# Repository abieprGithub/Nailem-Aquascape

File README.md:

# Nailem: Smart Aquascape

As the name suggests, N**ai**lem is an AIoT-powered highly automated aquascape maintenance system, originally designed for Nilem fish (Osteochilus Vittatus):

<br>

🐟 Why Nilem in particular?

1. They're awesome
2. They're tuff (as in they can live in harsh conditions)
3. They're edible (yum)
4. They're common in my nation (Indonesia!)
5. They're reasonably sized (for food fish, at least)

### ❗ But more importantly,
This is **not** limited only to Nilem fish, and it will be designed to be scalable and flexible to meet the living conditions of most other fish, across a wide range of scale.
Of course, community contributions help in adapting this to a wider range of fish, though I haven't given myself time to learn how to manage contributions yet.

I've came up with this to solve a very real problem:
1) Raising food fish is a challenging and long process
2) I'm lazy as hell
3) Urban farming shouldn't be limited to crops, but livestock too

## Quick navigation

[🛠️ Technical Functions](detailed-functions) | [⚠️ Disclaimers](disclaimer) | [📜 Bulletin](bulletin)

(doesn't work yet, my bad)

<br>

## ⚙️ Functions

*Note: The following 3D model is old, and I will make a new one from the ground up soon.*

## 🛠️ Technical
It packs a whole load of functions. At its core, it's split between two subsystems: Real time control & AI compute.
At its core is an ESP32-S3 as a real time controller, which is kind of a perfect fit for this since I ended up utilizing almost its full potential.
To clarify a bit, what I mean by 'AI' before is actually just computer vision.
For that, this can be fitted with pretty much any low power computer that has USB or UART support, preferably SBCs designed for edge AI.
The NVIDIA Jetson Orin or the Rasperry Pi 5 + AI HAT should work well.
The thing is, the real time subsystem can exist as a standalone system, omitting the computer vision features entirely if the budget didn't allow.
However, it's 2026 and IoT alone is getting a little bit outdated.

<br>

<br>

### Detailed functions

*Programming or build hasn't started yet, but this gives you an idea of what I wanted to create.* 

**Primary Automation Features:**
1) 💦 Surface cleaning
2) 🌡️ Temperature Regulation
3) 🥄 Feeding
4) 💡Lighting
5) 🔄 Water Change

**Monitored parameters:**
1) Water Temperature
2) Water pH
3) Water TDS
4) Water Turbidity
5) Ambient temperature
6) Ambient humidity
7) Ambient lighting
8) Power consumption

**IoT features:**
1) Web Dashboard
2) API
3) OTA Firmware Update
4) 

**AI Features:**
1) Fish behavior detection
2) Anomaly detection
3) Egg detection (hopefully 😭)

**Miscellaneous features for the sake of the developer and or the user**
1) Two status ARGB LEDs on the board
2) Header for an external ARGB
3) UART debug header
4) USB-C data-only receptacle
5) Highly modular design, both physically and electrically. 

## Disclaimer
This used to be my 8th grade engineering project. However, after the project officially closes, I was NOT satisfied with how this turned out (it was still under 50% done), so I took over this entire project after ensuring that my team is okay with it. 
With that, kudos to my goated team for their work, even though I was responsible for 80% of the technical work:

<br>

Abie (myself) - Programmer, leader; Akbar - Mechanic; Adzka - Mechanic; <br>
Nabil - Management; Shifa - Scientist; Kirana - Media;

<br>
This did technically start before the Hack Club Stardance YSWS, but the amount of revisions made AFTER it started make this practically a new project tbh.
However, I'm still going to state that this project started before the season anyways.

## Bulletin

*This section is intended to show the latest updates, devlogs, or things you should know, and is updated reguarly!*

### 15th of September 2026

While waiting for the PCB to arrive, I took some time to create the CAD of the Aquascape. <br>
P.S, I haven't pushed the CAD to main since it's a little too large, I'll optimize it. <br>
Currently, it has seen great progress and I have created a few things: <br>
1) The aquarium glass
2) Most of the surface cleaning gantry mechanism, which includes:
3) Stepper motor Bracket
4) Endstops
5) Frame
6) Pulleys
7) Ultrasonic sensor bracket
8) Control box

A lot of things are still yet to be implemented, so let things continue. <br>
Meanwhile, here are some latest pictures.

### 7th of September 2026

The main ESP32-S3 IO PCB iteslf has been completed, and has started its production on JLCPCB. It should arrive at my doorsteps within 10-15 days. Meanwhile, I'll be working on the CAD model of the Aquascape with all the time I had. <br>
It took a total of over 20 hours to make it pretty, both electrically, visually, and functionally, whilst also having the constraints of having to fit inside JLCPCB's economic 2 layer footprint so I don't get taxed by Indonesian customs. <br> <br>

Anyways, here are some 3D model and boardview screenshots!

<br>
Without components:

<br><br><br><br><br><br><br><br><br><br><br><br><br><br><br><br><br><br><br>

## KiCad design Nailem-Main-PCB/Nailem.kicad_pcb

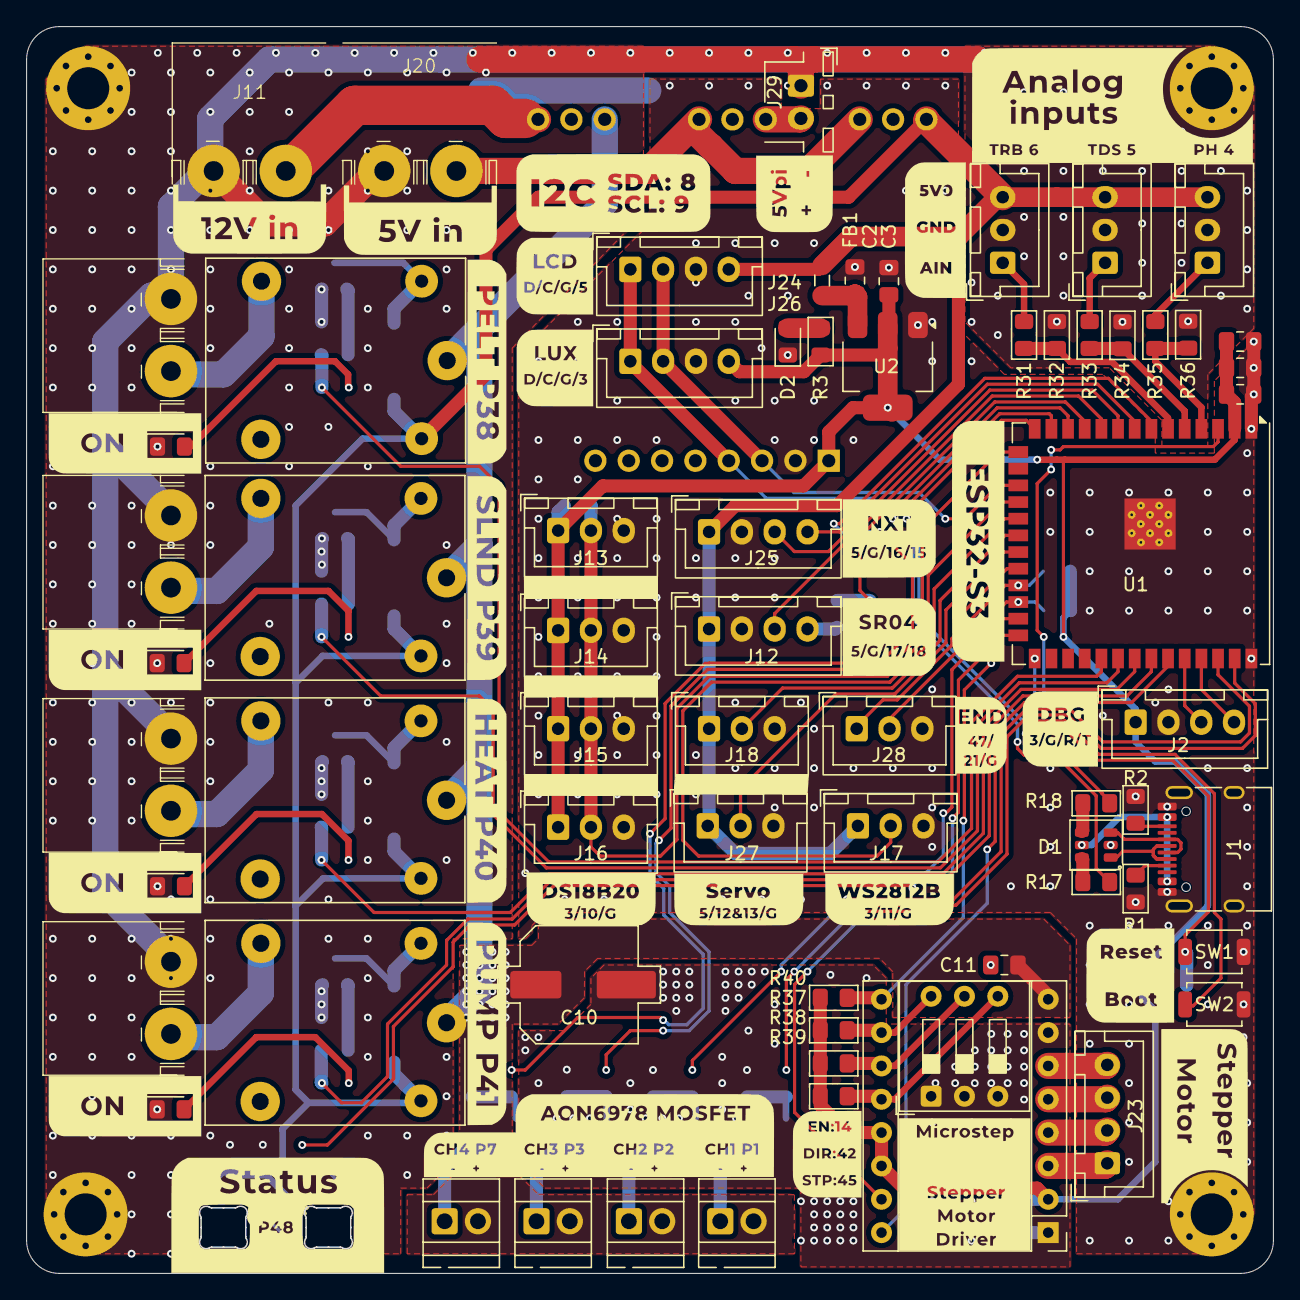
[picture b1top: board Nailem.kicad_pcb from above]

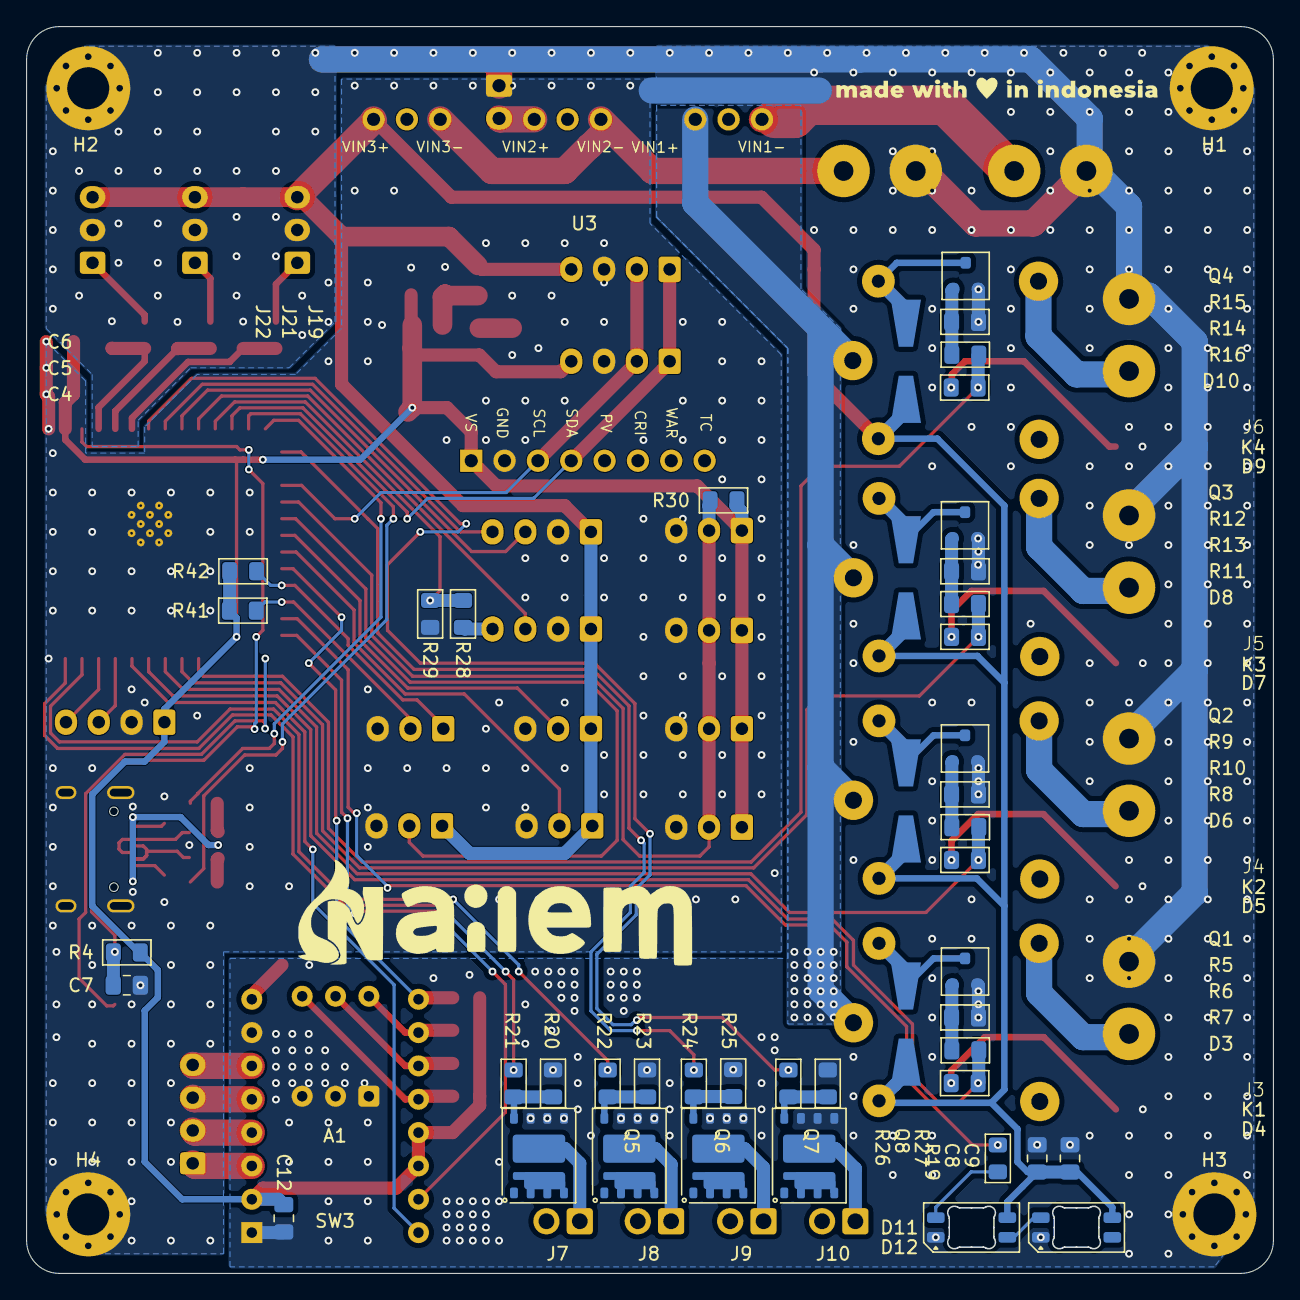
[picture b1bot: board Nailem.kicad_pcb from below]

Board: 2 copper layers, 95.0 x 95.0 mm, 118 parts (46 on the bottom side), 86 nets.

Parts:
A1: Pololu_Breakout_A4988; Pololu_Breakout-16_15.2x20.3mm
C2, C3, C4: 10uF; C_0805_2012Metric_Pad1.18x1.45mm_HandSolder
C5, C7: 1uF; C_0805_2012Metric_Pad1.18x1.45mm_HandSolder
C6, C8, C9, C11, C12: 100nF; C_0805_2012Metric_Pad1.18x1.45mm_HandSolder
C10: 100uF; C_Elec_8x10.2
D1: USBLC6-2SC6; SOT-23-6
D2, D4, D5, D7, D9: LED; LED_0805_2012Metric_Pad1.15x1.40mm_HandSolder
D3, D6, D8, D10: 1N4007; D_SMA-SMB_Universal_Handsoldering_NoSilk
D11, D12: SK6812MINI-E; LED_SK6812MINI-E_3.2x2.8mm_P1.5mm_ReverseMount
FB1: FerriteBead; L_0805_2012Metric_Pad1.05x1.20mm_HandSolder
H1, H2, H3, H4: MountingHole; MountingHole_3.2mm_M3_Pad_Via
J1: USB_OTG; USB_C_Receptacle_HRO_TYPE-C-31-M-12
J2: J_UART; JST_XH_B4B-XH-A_1x04_P2.50mm_Vertical
J3: OUT_CH1; 2EDGK_5.08_2P_M_NEW
J4: OUT_CH2; 2EDGK_5.08_2P_M_NEW
J5: OUT_CH3; 2EDGK_5.08_2P_M_NEW
J6: OUT_CH4; 2EDGK_5.08_2P_M_NEW
J7: LED_CH1; TerminalBlock_Xinya_XY308-2.54-2P_1x02_P2.54mm_Horizontal_N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
J8: LED_CH2; TerminalBlock_Xinya_XY308-2.54-2P_1x02_P2.54mm_Horizontal_N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
J9: LED_CH3; TerminalBlock_Xinya_XY308-2.54-2P_1x02_P2.54mm_Horizontal_N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
J10: LED_CH4; TerminalBlock_Xinya_XY308-2.54-2P_1x02_P2.54mm_Horizontal_N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
J11: 12VIN; 2EDGK_5.08_2P_M_NEW
J12: J_SR04; JST_XH_B4B-XH-A_1x04_P2.50mm_Vertical
J13: J_DS18B20_1; JST_XH_B3B-XH-A_1x03_P2.50mm_Vertical
J14: J_DS18B20_2; JST_XH_B3B-XH-A_1x03_P2.50mm_Vertical
J15: J_DS18B20_3; JST_XH_B3B-XH-A_1x03_P2.50mm_Vertical
J16: J_DS18B20_4; JST_XH_B3B-XH-A_1x03_P2.50mm_Vertical
J17: J_STATUS; JST_XH_B3B-XH-A_1x03_P2.50mm_Vertical
J18: J_SERVO; JST_XH_B3B-XH-A_1x03_P2.50mm_Vertical
J19: J_TURBIDITY; JST_XH_B3B-XH-A_1x03_P2.50mm_Vertical
J20: 5VIN; 2EDGK_5.08_2P_M_NEW
J21: J_TDS; JST_XH_B3B-XH-A_1x03_P2.50mm_Vertical
J22: J_PH; JST_XH_B3B-XH-A_1x03_P2.50mm_Vertical
J23: J_STEPPER; JST_XH_B4B-XH-A_1x04_P2.50mm_Vertical
J24: J_5V_LCD; JST_XH_B4B-XH-A_1x04_P2.50mm_Vertical
J25: J_5V_NEXTION; JST_XH_B4B-XH-A_1x04_P2.50mm_Vertical
J26: J_3V3_LUX; JST_XH_B4B-XH-A_1x04_P2.50mm_Vertical
J27: J_SERVO2; JST_XH_B3B-XH-A_1x03_P2.50mm_Vertical
J28: J_ENDS; JST_XH_B3B-XH-A_1x03_P2.50mm_Vertical
J29: 5VPI; JST_XH_B2B-XH-A_1x02_P2.50mm_Vertical
K1, K2, K3, K4: SANYOU_SRD_Form_C; Relay_SPDT_SANYOU_SRD_Series_Form_C_NoInSilk
Q1, Q2, Q3, Q4: MMBT2222A; SOT-23
Q5, Q6, Q7, Q8: AON6980; SO-8FL_DFN5x6
R1, R2: 5.1K; R_0805_2012Metric_Pad1.15x1.40mm_HandSolder
R3, R7, R8, R11, R14, R29, R32, R34, R36: 2K; R_0805_2012Metric_Pad1.15x1.40mm_HandSolder
R4, R20, R23, R25, R27, R37, R38, R39, R40, R41, R42: 10K; R_0805_2012Metric_Pad1.15x1.40mm_HandSolder
R5, R9, R12, R15: 100K; R_0805_2012Metric_Pad1.15x1.40mm_HandSolder
R6, R10, R13, R16, R28, R31, R33, R35: 1K; R_0805_2012Metric_Pad1.15x1.40mm_HandSolder
R17, R18: 33; R_0805_2012Metric_Pad1.15x1.40mm_HandSolder
R19: 220; R_0805_2012Metric_Pad1.15x1.40mm_HandSolder
R21, R22, R24, R26: 47; R_0805_2012Metric_Pad1.15x1.40mm_HandSolder
R30: 4.7K; R_0805_2012Metric_Pad1.15x1.40mm_HandSolder
SW1: SW_RST; SW_SPST_TS-1088-xR020
SW2: SW_BOOT; SW_SPST_TS-1088-xR020
SW3: SW_DIP_x03; SW_DIP_SPSTx03_Slide_9.78x9.8mm_W7.62mm_P2.54mm
U1: ESP32-S3-WROOM-1; ESP32-S3-WROOM-1U
U2: AMS1117-3.3; SOT-223-3_TabPin2
U3: INA3221_Module; INA3221_Module_P2.54mm_NoVPU_NoExtraGnds

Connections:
3V3LOGIC: A1.2 (VDD), A1.13 (~RESET), A1.14 (~SLEEP), C3.1, C4.1, C5.1, C6.1, C12.1, J2.1, J13.1, J14.1, J15.1, J16.1, J26.4, R3.2, R4.1, R30.1, R37.2, R38.2, R39.2, R40.2, R41.1, R42.1, U1.2 (3V3), U2.2 (VO), U3.1 (VS)
5VIN: C8.1, C9.1, D3.1 (K), D6.1 (K), D8.1 (K), D10.1 (K), D11.3 (VDD), D12.3 (VDD), FB1.1, J12.1, J17.1, J18.1, J19.3, J21.3, J22.3, J24.4, J25.1, J27.1, K1.5, K2.5, K3.5, K4.5, U3.14 (VIN3+)
5VPI: J29.2, U3.12 (VIN2+)
12V: A1.8 (VMOT), C10.1, C11.1, J7.2, J8.2, J9.2, J10.2, K1.1, K2.1, K3.1, K4.1, U3.10 (VIN1+)
CUR_N_CH1: J11.2, U3.9 (VIN1-)
CUR_N_CH2: J20.2, U3.11 (VIN2-), U3.13 (VIN3-)
DS18B20_BUS: J13.2, J14.2, J15.2, J16.2, R30.2, U1.18 (IO10)
END_XMIN: J28.1, R42.2, U1.23 (IO21)
END_XPLUS: J28.2, R41.2, U1.24 (IO47)
ESP_RX: J2.3, U1.36 (RXD0)
ESP_TX: J2.4, U1.37 (TXD0)
GND: A1.1 (GND), A1.7 (GND), C2.2, C3.2, C4.2, C5.2, C6.2, C7.2, C8.2, C9.2, C10.2, C11.2, C12.2, D1.2 (VN), D2.1 (K), D4.1 (K), D5.1 (K), D7.1 (K), D9.1 (K), D11.1 (VSS), D12.1 (VSS), H1.1 (1_1), H2.1 (1_1), H3.1 (1_1), H4.1 (1_1), J1.A1 (GND), J1.A12 (GND), J1.B1 (GND), J1.B12 (GND), J1.SH (SHIELD), J2.2, J3.2, J4.2, J5.2, J6.2, J11.1, J12.2, J13.3, J14.3, J15.3, J16.3, J17.3, J18.3, J19.2, J20.1, J21.2, J22.2, J24.3, J25.2, J26.3, J27.3, J28.3, J29.1, Q1.2 (E), Q2.2 (E), Q3.2 (E), Q4.2 (E), Q5.3 (S2), Q5.4 (S2), Q5.5 (S2), Q6.3 (S2), Q6.4 (S2), Q6.5 (S2), Q7.3 (S2), Q7.4 (S2), Q7.5 (S2), Q8.3 (S2), Q8.4 (S2), Q8.5 (S2), R1.1, R2.1, R5.1, R9.1, R12.1, R15.1, R20.2, R23.2, R25.2, R27.2, R29.1, R32.1, R34.1, R36.1, SW1.1 (A), SW2.1 (A), SW3.1, SW3.2, SW3.3, U1.1 (GND), U1.40 (GND), U1.41 (GND), U2.1 (GND), U3.2 (GND)
HCSR04_ECHO: R28.2, R29.2, U1.11 (IO18)
HCSR04_TRIG: J12.3, U1.10 (IO17)
I2C_SCL: J24.2, J26.2, U1.17 (IO9), U3.3 (SCL)
I2C_SDA: J24.1, J26.1, U1.12 (IO8), U3.4 (SDA)
IND_ARGB: R19.1, U1.25 (IO48)
LED_DRV_CH1: R21.1, U1.39 (IO1)
LED_DRV_CH2: R22.1, U1.38 (IO2)
LED_DRV_CH3: R24.1, U1.15 (IO3)
LED_DRV_CH4: R26.1, U1.7 (IO7)
NX_RX: J25.3, U1.9 (IO16)
NX_TX: J25.4, U1.8 (IO15)
unnamed: A1.4 (1A), J23.2
unnamed: A1.3 (1B), J23.1
unnamed: A1.5 (2A), J23.3
unnamed: A1.6 (2B), J23.4
unnamed: A1.10 (MS1), R37.1, SW3.6
unnamed: A1.11 (MS2), R38.1, SW3.5
unnamed: A1.12 (MS3), R39.1, SW3.4
unnamed: D1.1 (L1), J1.A7 (D-), J1.B7 (D-)
unnamed: D1.3 (L2), J1.A6 (D+), J1.B6 (D+)
unnamed: D1.5 (VP), J1.A4 (VBUS), J1.A9 (VBUS), J1.B4 (VBUS), J1.B9 (VBUS)
unnamed: D2.2 (A), R3.1
unnamed: D3.2 (A), K1.2, Q1.3 (C)
unnamed: D4.2 (A), R7.1
unnamed: D5.2 (A), R8.1
unnamed: D6.2 (A), K2.2, Q2.3 (C)
unnamed: D7.2 (A), R11.1
unnamed: D8.2 (A), K3.2, Q3.3 (C)
unnamed: D9.2 (A), R14.1
unnamed: D10.2 (A), K4.2, Q4.3 (C)
unnamed: D11.2 (DIN), R19.2
unnamed: D11.4 (DOUT), D12.2 (DIN)
unnamed: J1.A5 (CC1), R1.2
unnamed: J1.B5 (CC2), R2.2
unnamed: J3.1, K1.3
unnamed: J4.1, K2.3
unnamed: J5.1, K3.3
unnamed: J6.1, K4.3
unnamed: J7.1, Q5.7 (C)
unnamed: J8.1, Q6.7 (C)
unnamed: J9.1, Q7.7 (C)
unnamed: J10.1, Q8.7 (C)
unnamed: J12.4, R28.1
unnamed: J19.1, R31.2
unnamed: J21.1, R33.2
unnamed: J22.1, R35.2
unnamed: Q1.1 (B), R5.2, R6.2
unnamed: Q2.1 (B), R9.2, R10.2
unnamed: Q3.1 (B), R12.2, R13.2
unnamed: Q4.1 (B), R15.2, R16.2
unnamed: Q5.6 (G2), R20.1, R21.2
unnamed: Q6.6 (G2), R22.2, R23.1
unnamed: Q7.6 (G2), R24.2, R25.1
unnamed: Q8.6 (G2), R26.2, R27.1
unnamed: C7.1, R4.2, SW1.2 (B), U1.3 (EN)
unnamed: SW2.2 (B), U1.27 (IO0)
unnamed: R18.2, U1.14 (USB_D+)
unnamed: R17.2, U1.13 (USB_D-)
unnamed: C2.1, FB1.2, U2.3 (VI)
OTG_DN: D1.6 (L1), R17.1
OTG_DP: D1.4 (L2), R18.1
PH_Ain: R35.1, R36.2, U1.4 (IO4)
RELAY_CH1: R6.1, R7.2, U1.34 (IO41)
RELAY_CH2: R8.2, R10.1, U1.33 (IO40)
RELAY_CH3: R11.2, R13.1, U1.32 (IO39)
RELAY_CH4: R14.2, R16.1, U1.31 (IO38)
SERVO2_PWM: J27.2, U1.21 (IO13)
SERVO_PWM: J18.2, U1.20 (IO12)
STEP_DIR: A1.16 (DIR), U1.35 (IO42)
STEP_EN: A1.9 (~ENABLE), R40.1, U1.22 (IO14)
STEP_STP: A1.15 (STEP), U1.26 (IO45)
TDS_Ain: R33.1, R34.2, U1.5 (IO5)
TURB_Ain: R31.1, R32.2, U1.6 (IO6)
WS2812_BUS: J17.2, U1.19 (IO11)

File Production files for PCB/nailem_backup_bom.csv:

Designator,Footprint,Quantity,Value,LCSC Part #
A1,Pololu_Breakout-16_15.2x20.3mm,1,Pololu_Breakout_A4988,
C10,C_Elec_8x10.2,1,100uF,
"C11, C12, C6, C8, C9",0805,5,100nF,
"C2, C3, C4",0805,3,10uF,
"C5, C7",0805,2,1uF,
D1,SOT-23-6,1,USBLC6-2SC6,
"D10, D3, D6, D8",D_SMA-SMB_Universal_Handsoldering_NoSilk,4,1N4007,
"D11, D12",LED_SK6812MINI-E_3.2x2.8mm_P1.5mm_ReverseMount,2,SK6812MINI-E,
"D2, D4, D5, D7, D9",0805,5,LED,
FB1,0805,1,FerriteBead,
J1,USB_C_Receptacle_HRO_TYPE-C-31-M-12,1,USB_OTG,
J10,TerminalBlock_Xinya_XY308-2.54-2P_1x02_P2.54mm_Horizontal_NoTriangle,1,LED_CH4,
J11,2EDGK_5.08_2P_M_NEW,1,12VIN,
J12,JST_XH_B4B-XH-A_1x04_P2.50mm_Vertical,1,J_SR04,
J13,JST_XH_B3B-XH-A_1x03_P2.50mm_Vertical,1,J_DS18B20_1,
J14,JST_XH_B3B-XH-A_1x03_P2.50mm_Vertical,1,J_DS18B20_2,
J15,JST_XH_B3B-XH-A_1x03_P2.50mm_Vertical,1,J_DS18B20_3,
J16,JST_XH_B3B-XH-A_1x03_P2.50mm_Vertical,1,J_DS18B20_4,
J17,JST_XH_B3B-XH-A_1x03_P2.50mm_Vertical,1,J_STATUS,
J18,JST_XH_B3B-XH-A_1x03_P2.50mm_Vertical,1,J_SERVO,
J19,JST_XH_B3B-XH-A_1x03_P2.50mm_Vertical,1,J_TURBIDITY,
J2,JST_XH_B4B-XH-A_1x04_P2.50mm_Vertical,1,J_UART,
J20,2EDGK_5.08_2P_M_NEW,1,5VIN,
J21,JST_XH_B3B-XH-A_1x03_P2.50mm_Vertical,1,J_TDS,
J22,JST_XH_B3B-XH-A_1x03_P2.50mm_Vertical,1,J_PH,
J23,JST_XH_B4B-XH-A_1x04_P2.50mm_Vertical,1,J_STEPPER,
J24,JST_XH_B4B-XH-A_1x04_P2.50mm_Vertical,1,J_5V_LCD,
J25,JST_XH_B4B-XH-A_1x04_P2.50mm_Vertical,1,J_5V_NEXTION,
J26,JST_XH_B4B-XH-A_1x04_P2.50mm_Vertical,1,J_3V3_LUX,
J27,JST_XH_B3B-XH-A_1x03_P2.50mm_Vertical,1,J_SERVO2,
J28,JST_XH_B3B-XH-A_1x03_P2.50mm_Vertical,1,J_ENDS,
J29,JST_XH_B2B-XH-A_1x02_P2.50mm_Vertical,1,5VPI,
J3,2EDGK_5.08_2P_M_NEW,1,OUT_CH1,
J4,2EDGK_5.08_2P_M_NEW,1,OUT_CH2,
J5,2EDGK_5.08_2P_M_NEW,1,OUT_CH3,
J6,2EDGK_5.08_2P_M_NEW,1,OUT_CH4,
J7,TerminalBlock_Xinya_XY308-2.54-2P_1x02_P2.54mm_Horizontal_NoTriangle,1,LED_CH1,
J8,TerminalBlock_Xinya_XY308-2.54-2P_1x02_P2.54mm_Horizontal_NoTriangle,1,LED_CH2,
J9,TerminalBlock_Xinya_XY308-2.54-2P_1x02_P2.54mm_Horizontal_NoTriangle,1,LED_CH3,
"K1, K2, K3, K4",Relay_SPDT_SANYOU_SRD_Series_Form_C_NoInSilk,4,SANYOU_SRD_Form_C,
"Q1, Q2, Q3, Q4",SOT-23,4,MMBT2222A,
"Q5, Q6, Q7, Q8",SO-8FL_DFN5x6,4,AON6980,
"R1, R2",0805,2,5.1K,
"R10, R13, R16, R28, R31, R33, R35, R6",0805,8,1K,
"R11, R14, R29, R3, R32, R34, R36, R7, R8",0805,9,2K,
"R12, R15, R5, R9",0805,4,100K,
"R17, R18",0805,2,33,
R19,0805,1,220,
"R20, R23, R25, R27, R37, R38, R39, R4, R40, R41, R42",0805,11,10K,
"R21, R22, R24, R26",0805,4,47,
R30,0805,1,4.7K,
SW1,SW_SPST_TS-1088-xR020,1,SW_RST,
SW2,SW_SPST_TS-1088-xR020,1,SW_BOOT,
SW3,SW_DIP_SPSTx03_Slide_9.78x9.8mm_W7.62mm_P2.54mm,1,SW_DIP_x03,
U1,ESP32-S3-WROOM-1U,1,ESP32-S3-WROOM-1,
U2,SOT-223-3_TabPin2,1,AMS1117-3.3,
U3,INA3221_Module_P2.54mm_NoVPU_NoExtraGnds,1,INA3221_Module,
